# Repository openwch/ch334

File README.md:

# ch334
Share the schematic and layout (KiCad) for DIY USB2.0 4-PORTS HUB with CH334U

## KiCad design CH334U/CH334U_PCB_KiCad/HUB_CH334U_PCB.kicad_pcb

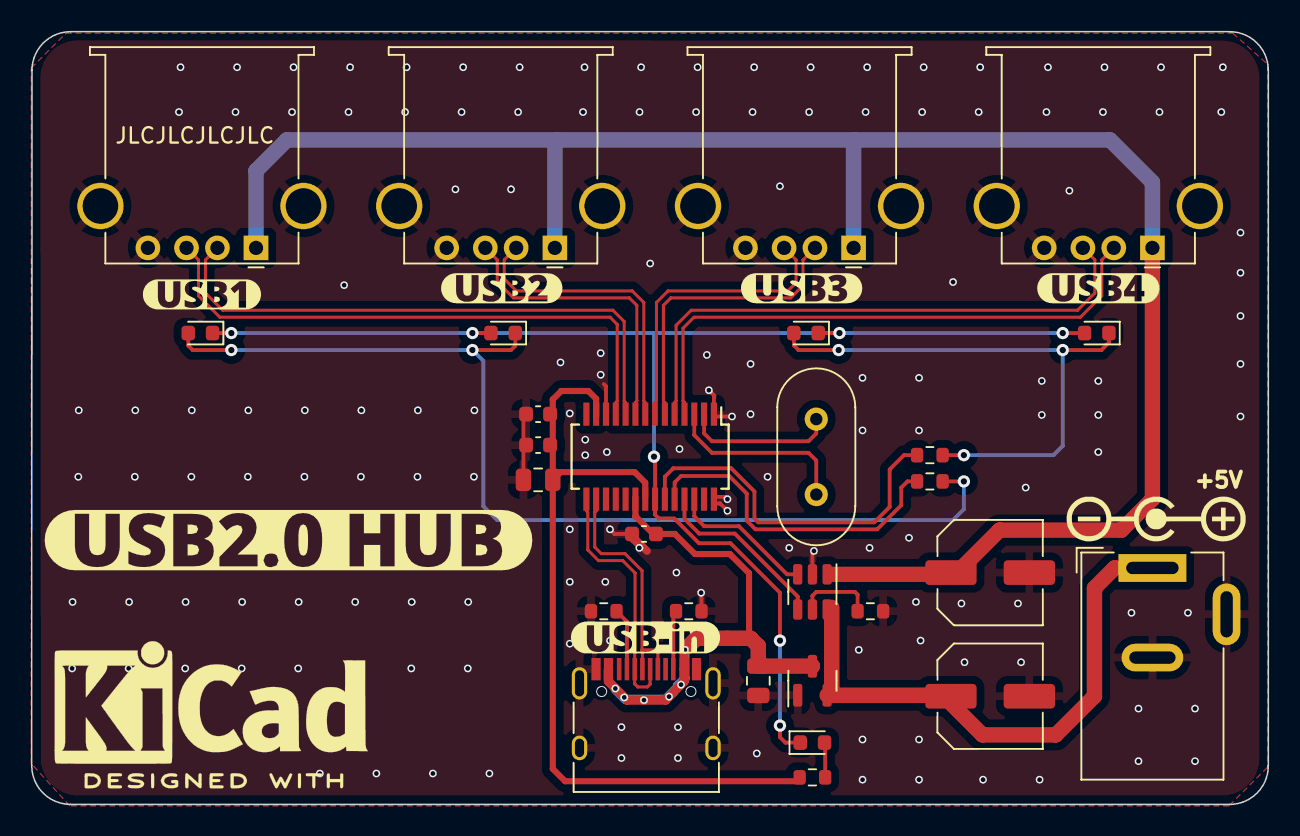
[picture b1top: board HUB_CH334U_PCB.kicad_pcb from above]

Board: 2 copper layers, 80.0 x 50.0 mm, 34 parts (0 on the bottom side), 28 nets.

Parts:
C1, C4: 10uF; C_0805_2012Metric
C2, C7: 330uF; C_Elec_6.3x5.8
C3, C6: 1uF; C_0603_1608Metric
C5: 0.1uF; C_0603_1608Metric
D1: RED; LED_0603_1608Metric
D2: GREEN_1; LED_0603_1608Metric
D3: GREEN_2; LED_0603_1608Metric
D4: GREEN_3; LED_0603_1608Metric
D5: GREEN_4; LED_0603_1608Metric
J1: USB_C_Receptacle_USB2.0; USB_C_Receptacle_HRO_TYPE-C-31-M-12
J2: Barrel_Jack_Switch; BarrelJack_Wuerth_6941xx301002
J3, J4, J5, J6: USB_A; USB_A_Stewart_SS-52100-001_Horizontal
R1, R2: 5.1k; R_0603_1608Metric
R3: 470; R_0603_1608Metric
R4, R5: 220; R_0603_1608Metric
R6: 47k; R_0603_1608Metric
U1: CH213K; SOT-23
U2: CH334U; SSOP-28_3.9x9.9mm_P0.635mm
U3: CH217K; SOT-23-6
Y1: 12MHz; Crystal_HC49-4H_Vertical
kibuzzard-640064AB: G***; kibuzzard-640064AB
kibuzzard-6400647B: G***; kibuzzard-6400647B
kibuzzard-64006469: G***; kibuzzard-64006469
kibuzzard-64006482: G***; kibuzzard-64006482
kibuzzard-64006489: G***; kibuzzard-64006489
kibuzzard-64006497: G***; kibuzzard-64006497

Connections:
+5V: C2.1, J2.1, U1.2 (VO), U3.6 (VIN)
/3v3: C3.2, C4.2, C5.2, R3.2, U2.13 (VDD33), U2.21 (VDD33)
/LED1: R5.2, U2.23 (LED1)
/LED2: R4.2, U2.24 (LED2)
/LED4: D1.1 (K), D2.1 (K), D3.2 (A), D4.1 (K), D5.2 (A), U2.22 (LED4/SDA)
/OVCUR: U2.26 (OVCUR#), U3.3 (FLAG#)
/PWREN: U2.25 (PWREN#), U3.4 (EN#)
/UP_D+: J1.A6 (D+), J1.B6 (D+), U2.16 (DPU)
/UP_D-: J1.A7 (D-), J1.B7 (D-), U2.15 (DMU)
/USB1_D+: J3.3 (D+), U2.11 (DP1)
/USB1_D-: J3.2 (D-), U2.10 (DM1)
/USB2_D+: J4.3 (D+), U2.9 (DP2)
/USB2_D-: J4.2 (D-), U2.8 (DM2)
/USB3_D+: J5.3 (D+), U2.7 (DP3)
/USB3_D-: J5.2 (D-), U2.6 (DM3)
/USB4_D+: J6.3 (D+), U2.5 (DP4)
/USB4_D-: J6.2 (D-), U2.4 (DM4)
/VBUS_IN: C1.1, C6.2, J1.A4 (VBUS), J1.A9 (VBUS), J1.B4 (VBUS), J1.B9 (VBUS), U1.3 (VI), U2.20 (V5)
GND: C1.2, C2.2, C3.1, C4.1, C5.1, C6.1, C7.2, J1.A1 (GND), J1.A12 (GND), J1.B1 (GND), J1.B12 (GND), J1.S1 (SHIELD), J2.2, J2.3, J3.4 (GND), J3.5 (Shield), J4.4 (GND), J4.5 (Shield), J5.4 (GND), J5.5 (Shield), J6.4 (GND), J6.5 (Shield), R1.2, R2.2, R6.1, U1.1 (GND), U2.1 (GND), U2.12 (GND), U2.28 (GND), U3.2 (GND)
unnamed: D1.2 (A), R3.1
unnamed: D2.2 (A), D3.1 (K), R4.1
unnamed: D4.2 (A), D5.1 (K), R5.1
unnamed: J1.A5 (CC1), R1.1
unnamed: J1.B5 (CC2), R2.1
unnamed: U2.3 (XI), Y1.1
unnamed: U2.2 (XO), Y1.2
unnamed: R6.2, U3.5 (ISET)
VBUS: C7.1, J3.1 (VBUS), J4.1 (VBUS), J5.1 (VBUS), J6.1 (VBUS), U3.1 (VOUT)

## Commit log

2023-03-09 add ch334u pcb files
